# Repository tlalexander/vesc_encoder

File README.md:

# vesc_encoder
An openly licensed magnetic encoder board, compatible with VESC 4.12 based designs.

The data in this repository is licensed CC0, which generally means "Public Domain".
https://creativecommons.org/publicdomain/zero/1.0/

In other words: this information can be used for any purpose.

# Screenshots

# Use
These files are made for KiCAD and an AS5047 encoder.

You'll need to use a firmware file with the "Use Hardware SPI" option enabled at compile time using the #defines in the config files.

# External links
See others who have used this encoder chip:
http://www.electric-skateboard.builders/t/my-vesc-with-as5047-sensor-setup/6568

And documentation on how I use it:
https://reboot.love/t/vesc-mods-for-robotics-use/

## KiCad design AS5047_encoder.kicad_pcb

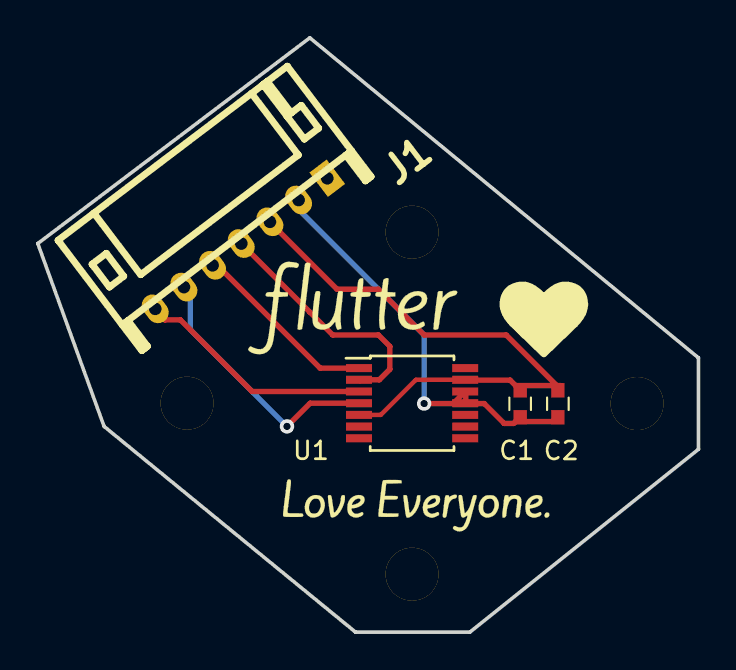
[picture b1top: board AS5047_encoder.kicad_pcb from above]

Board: 2 copper layers, 36.7 x 33.0 mm, 4 parts (0 on the bottom side), 6 nets.

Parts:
C1, C2: C_0603
J1: s7b-ph-kl
U1: AS5047; TSSOP-14_4.4x5mm_Pitch0.65mm

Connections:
/CLK: J1.4, U1.2
/CSn: J1.5, U1.1
/MISO: J1.7, U1.3
/MOSI: J1.6, U1.4
/VCC: C1.1, C2.1, J1.2, U1.11, U1.12
GND: C1.2, C2.2, J1.3, U1.5, U1.13

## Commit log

2018-01-09 Change connector and update component associations.
2018-01-17 Fixed outline. Generated gerbers. Added BOM. Ordered a batch of boards.
2019-01-26 Imported to a new Kicad install and removed remnant traces from PCB layout. Suggest re-export gerbers to remove benign extra trace.
2019-01-26 Update docs. Add screenshots and link to reboot.
